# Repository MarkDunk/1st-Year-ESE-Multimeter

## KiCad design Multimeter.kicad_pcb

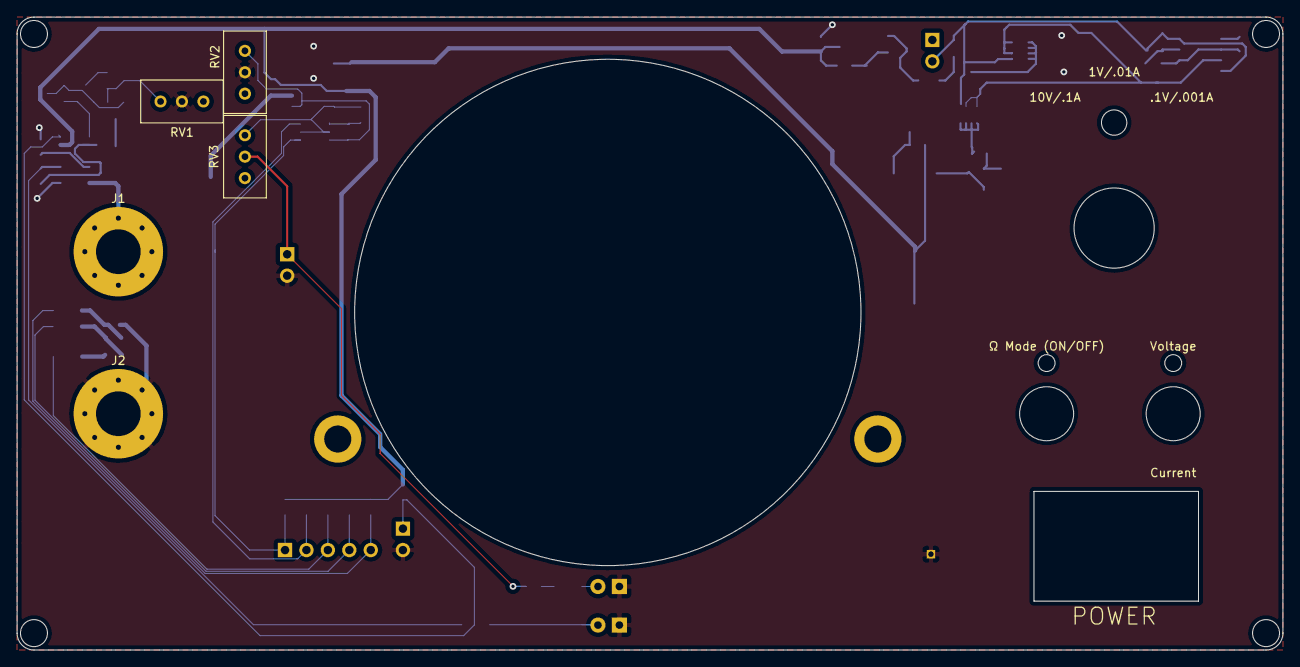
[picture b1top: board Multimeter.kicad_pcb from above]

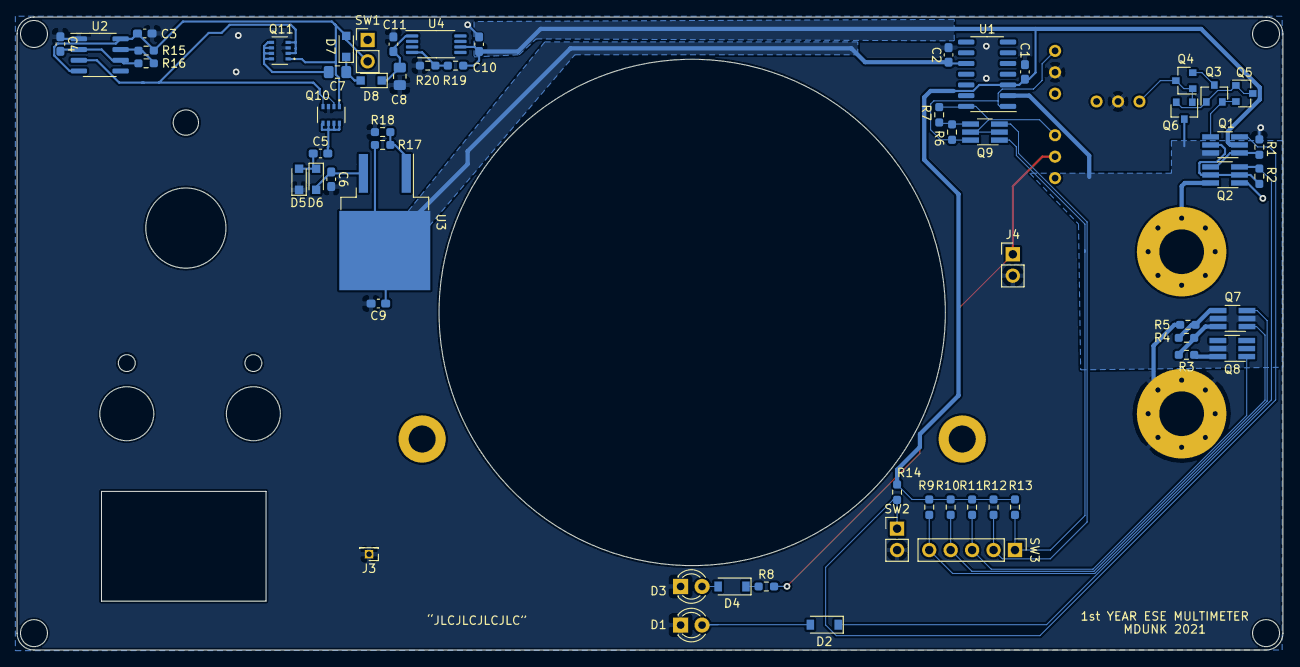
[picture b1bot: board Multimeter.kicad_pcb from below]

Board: 2 copper layers, 150.0 x 75.0 mm, 64 parts (59 on the bottom side), 40 nets.

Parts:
C1, C2, C11: .1uF; C_0603_1608Metric_Pad1.08x0.95mm_HandSolder
C3: .01uF; C_0603_1608Metric_Pad1.08x0.95mm_HandSolder
C4: 100pF; C_0603_1608Metric_Pad1.08x0.95mm_HandSolder
C5, C6, C9, C10: 1uF; C_0603_1608Metric_Pad1.08x0.95mm_HandSolder
C7, C8: 22uF; C_0805_2012Metric_Pad1.18x1.45mm_HandSolder
D1, D3: LED; LED_D3.0mm
D2, D4: MMSZ5238B; D_SOD-123
D5, D6, D7, D8: CUS520; D_SOD-323_HandSoldering
J1, J2: Conn_01x01; MountingHole_5.3mm_M5_Pad_Via
J3: Conn_01x01; PinHeader_1x01_P1.27mm_Vertical
J4: Screw_Terminal_01x02; PinHeader_1x02_P2.54mm_Vertical
Q1, Q2, Q7, Q8, Q9: SQ3989EV; TSOT-23-6_HandSoldering
Q3, Q4, Q5, Q6: MMBT3906; SOT-23
Q10, Q11: TT8M3TR; TT8M3
R1: 1k; R_0603_1608Metric_Pad0.98x0.95mm_HandSolder
R2, R8: 470; R_0603_1608Metric_Pad0.98x0.95mm_HandSolder
R3: 90.9; R_0603_1608Metric_Pad0.98x0.95mm_HandSolder
R4: 9; R_0603_1608Metric_Pad0.98x0.95mm_HandSolder
R5: 1; R_0603_1608Metric_Pad0.98x0.95mm_HandSolder
R6, R9, R10, R11, R12, R14: 27k; R_0603_1608Metric_Pad0.98x0.95mm_HandSolder
R7: 270k; R_0603_1608Metric_Pad0.98x0.95mm_HandSolder
R13: 5x27k; R_0603_1608Metric_Pad0.98x0.95mm_HandSolder
R15, R16: 10k; R_0603_1608Metric_Pad0.98x0.95mm_HandSolder
R17: 5.6k; R_0603_1608Metric_Pad0.98x0.95mm_HandSolder
R18: 12k; R_0603_1608Metric_Pad0.98x0.95mm_HandSolder
R19: 8.2k; R_0603_1608Metric_Pad0.98x0.95mm_HandSolder
R20: 56k; R_0603_1608Metric_Pad0.98x0.95mm_HandSolder
RV1: 10k; Potentiometer_Bourns_3296W_Vertical
RV2: 5k; Potentiometer_Bourns_3296W_Vertical
RV3: 100k; Potentiometer_Bourns_3296W_Vertical
SW1, SW2: SW_SPST; PinHeader_1x02_P2.54mm_Vertical
SW3: SW_Rotary2x6; PinHeader_1x05_P2.54mm_Vertical
U1: TLV274CDR; SOIC-14_3.9x8.7mm_P1.27mm
U2: NE555D; SOIC-8_3.9x4.9mm_P1.27mm
U3: LM337_TO263; TO-263-2
U4: LM317LPW; TSSOP-8_4.4x3mm_P0.65mm

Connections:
/1V_SW: Q9.3, R12.2, SW3.2
/10V_SW: Q9.1, R13.2, SW3.1
/.001A_SW: Q7.3, R9.2, SW3.6
/.01A_SW: Q7.1, R10.2, SW3.5
/.1A_SW: Q8.1, R11.2, SW3.4
/Power/CLK: Q10.2, Q10.4, Q11.2, Q11.4, U2.3
/Power/Vbat: C3.1, D7.2, Q10.1, Q11.1, R15.1, SW1.2, U2.4, U2.8
/R_SW: Q1.3, R14.2, SW2.1
/V+: J1.1, Q2.6
/Vdd: C1.2, C10.1, Q1.2, R9.1, R10.1, R11.1, R12.1, R13.1, R14.1, R19.2, U1.3, U4.6
/Vin: Q1.6, Q6.3, Q7.2, Q7.5, Q8.5, U1.2
/Vss: C2.1, C9.1, R17.2, U1.10, U3.2
GND: C1.1, C2.2, C3.2, C4.1, C6.2, C8.2, C9.2, C10.2, C11.2, D1.1, D3.1, D5.1, J2.1, J3.1, J4.2, Q2.1, Q10.3, Q11.3, R1.2, R5.2, R18.1, R20.1, RV1.2, RV2.2, SW2.2, U2.1
unnamed: C4.2, R16.2, U2.2, U2.6
unnamed: C5.1, D5.2, D6.1
unnamed: C5.2, Q10.5, Q10.6, Q10.7, Q10.8
unnamed: C6.1, D6.2, U3.3
unnamed: C7.1, D7.1, D8.2
unnamed: C7.2, Q11.5, Q11.6, Q11.7, Q11.8
unnamed: C8.1, C11.1, D8.1, U4.1
unnamed: D1.2, D2.2
unnamed: D2.1, Q2.3, R2.2
unnamed: D3.2, D4.2
unnamed: D4.1, R8.1
unnamed: J4.1, R8.2, RV3.2
unnamed: Q1.1, Q2.4, R1.1
unnamed: Q1.4, Q3.2, Q5.2
unnamed: Q1.5, Q2.2, Q2.5, R2.1
unnamed: Q3.1, Q5.1, Q5.3, Q6.2
unnamed: Q3.3, Q4.2
unnamed: Q4.1, Q4.3, Q6.1, RV1.1
unnamed: Q7.4, R4.2, R5.1
unnamed: Q7.6, R3.2, R4.1
unnamed: Q8.6, R3.1
unnamed: Q9.2, Q9.5, R7.1, RV3.1, U1.14
unnamed: Q9.4, R6.1, R7.2
unnamed: Q9.6, R6.2, RV2.1, U1.1
unnamed: R15.2, R16.1, U2.7
unnamed: R17.1, R18.2, U3.1
unnamed: R19.1, R20.2, U4.4

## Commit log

2021-10-18 First version of the multimeter.
    This is the first complete version.
2021-10-22 Fixed symbol mismatch
    The pins for the TLV274 symbol were incorrect.
